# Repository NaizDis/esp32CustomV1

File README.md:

# esp32CustomV1
Custom esp32 model for personal Projects

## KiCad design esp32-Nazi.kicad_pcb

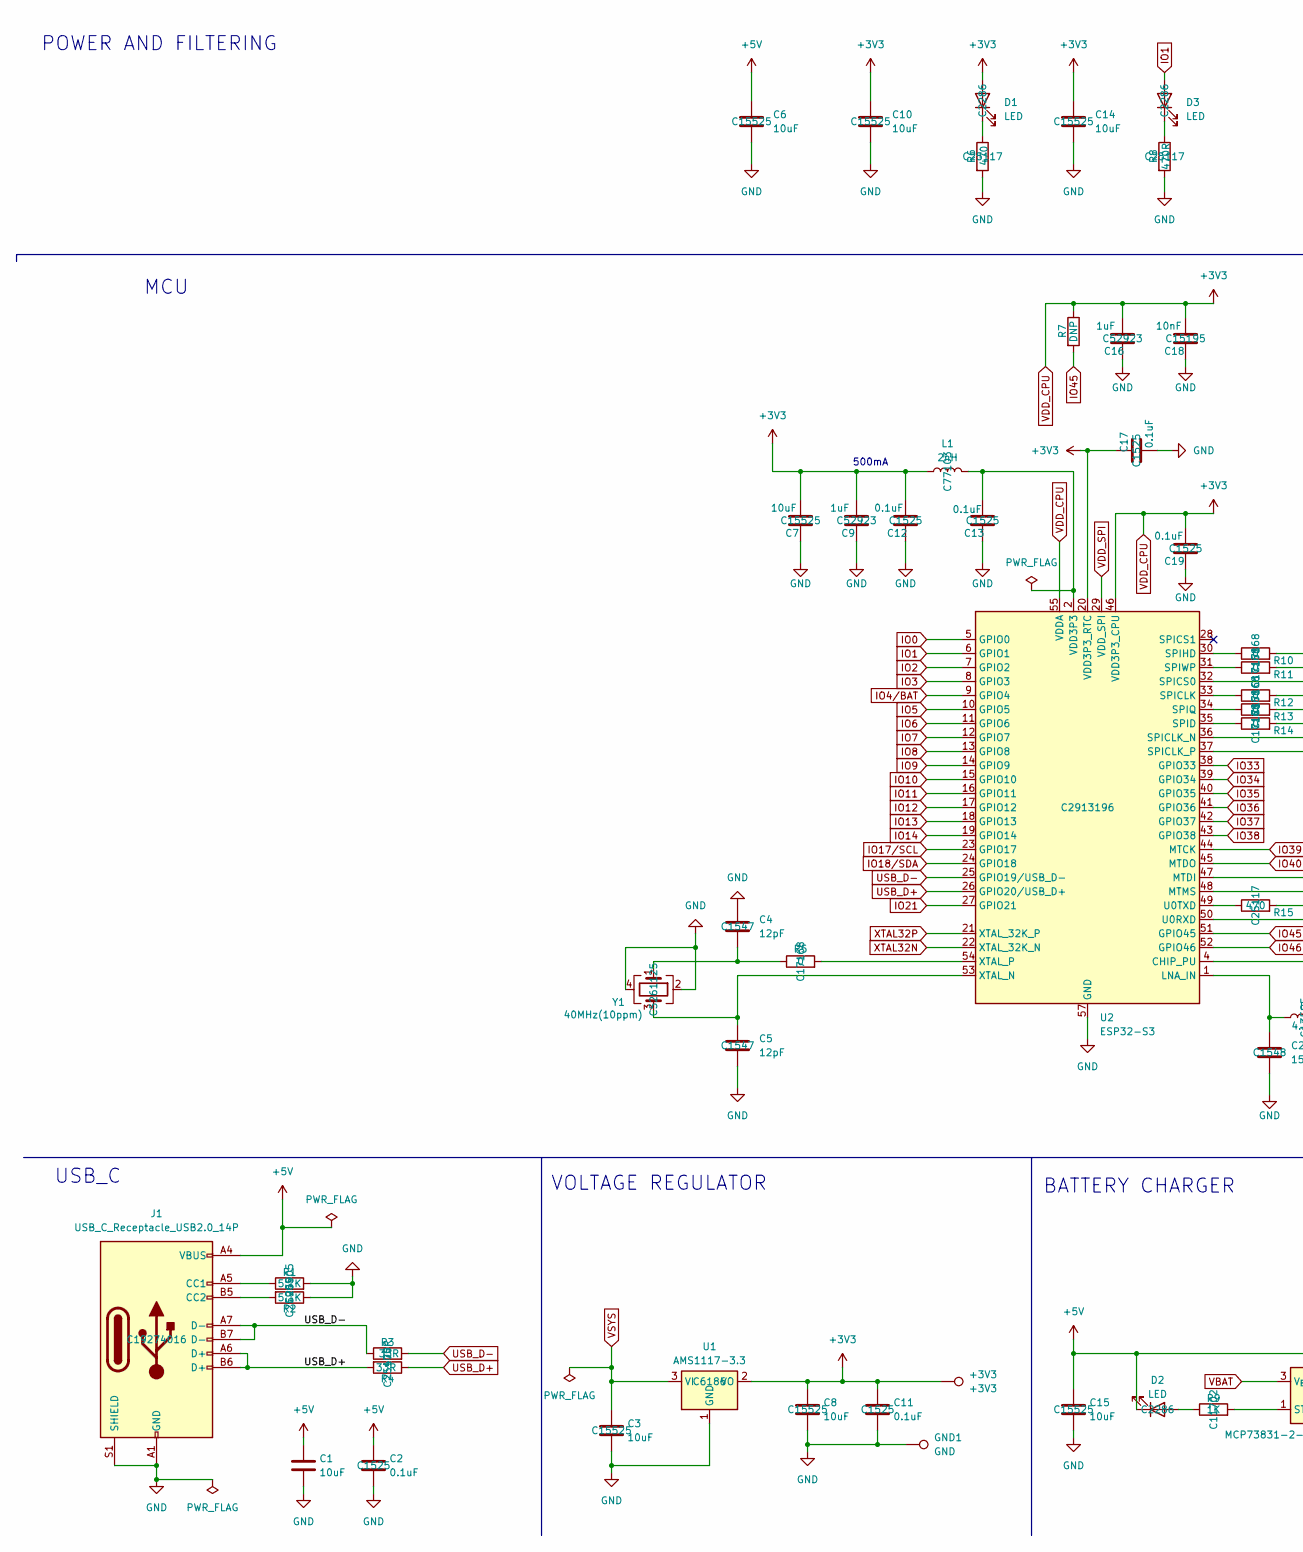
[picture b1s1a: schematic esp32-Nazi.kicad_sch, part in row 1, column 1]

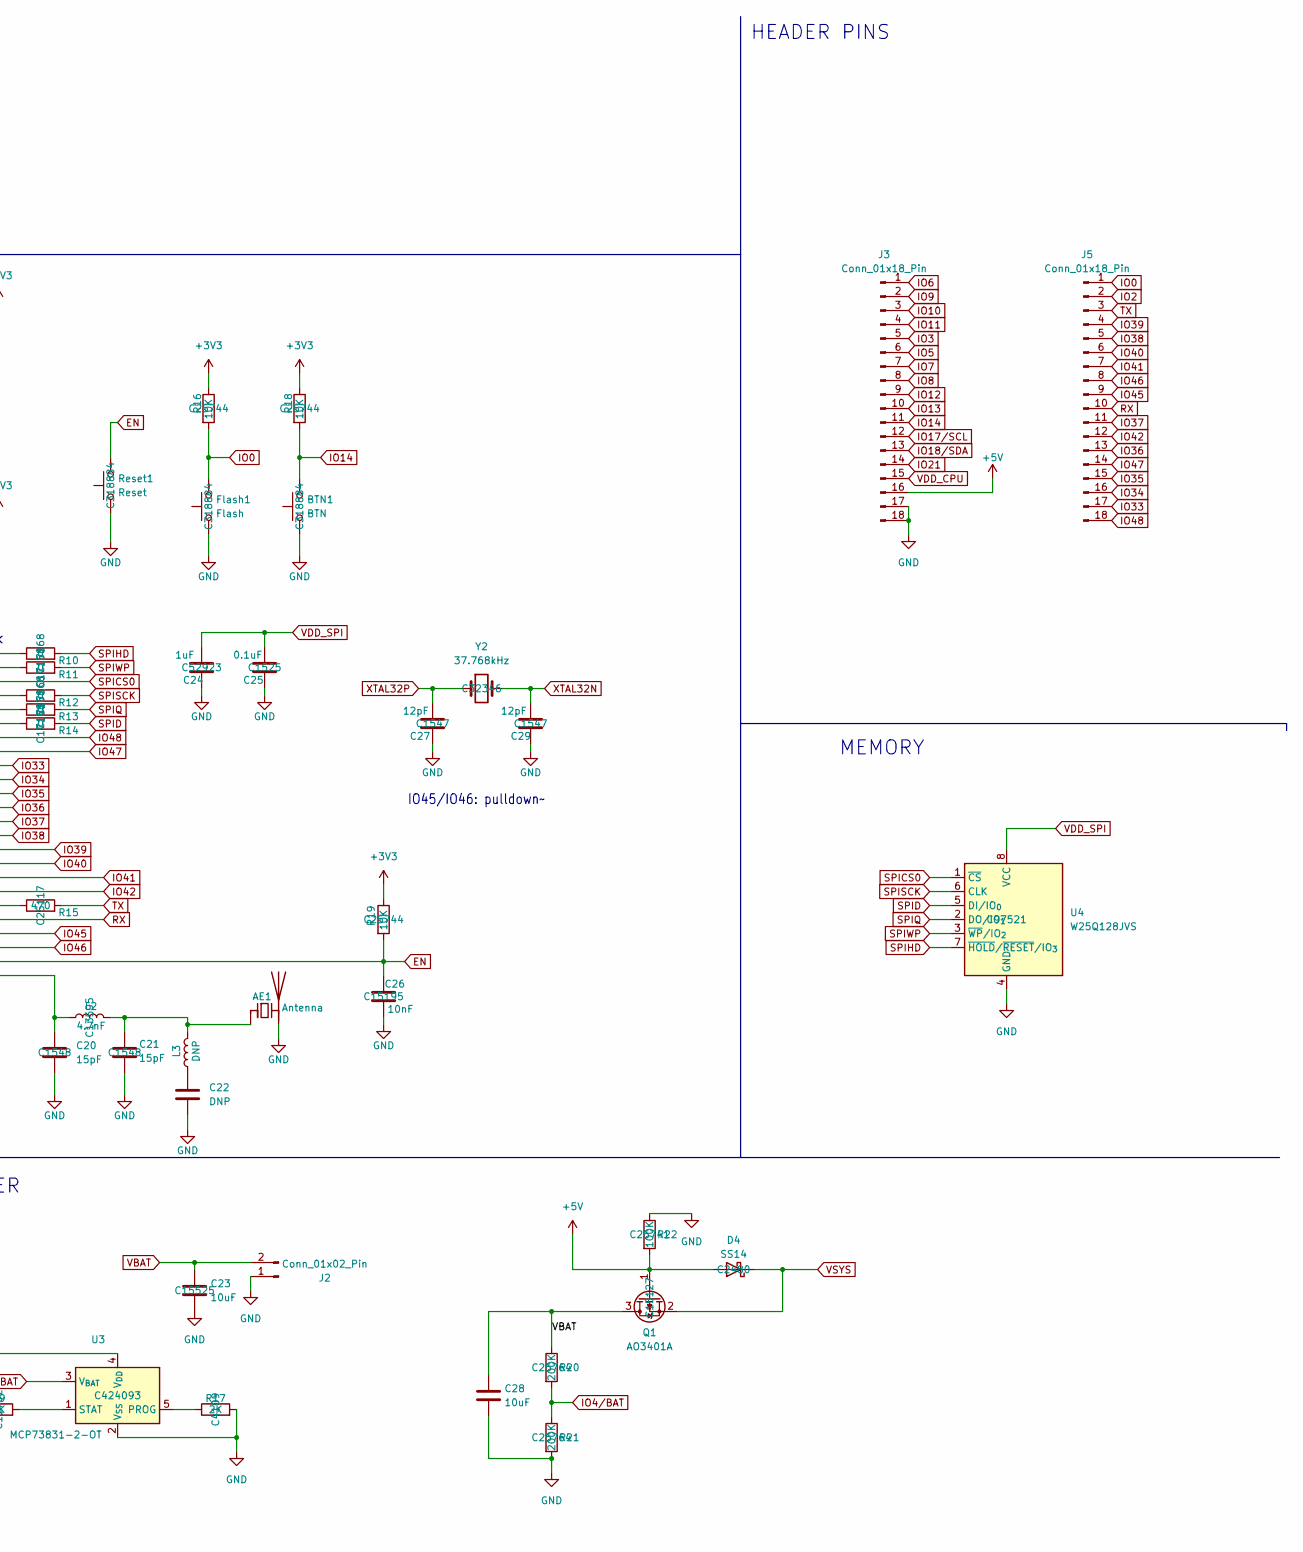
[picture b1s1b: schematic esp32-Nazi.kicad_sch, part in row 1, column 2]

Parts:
+3V3: +3V3; TestPoint_Pad_D1.0mm
AE1: Antenna; Texas_SWRA117D_2.4GHz_Left
BTN1: BTN; SW_Push_1P1T_XKB_TS-1187A; MNF PART NUMBER C318884
C1, C28: 10uF; C_0402_1005Metric
C2, C11, C12, C13, C17, C19, C25: 0.1uF; C_0402_1005Metric; MNF PART NUMBER C1525
C3, C6, C7, C8, C10, C14, C15, C23: 10uF; C_0402_1005Metric; MNF PART NUMBER C15525
C4, C5, C27, C29: 12pF; C_0402_1005Metric; MNF PART NUMBER C1547
C9, C16, C24: 1uF; C_0402_1005Metric; MNF PART NUMBER C52923
C18, C26: 10nF; C_0402_1005Metric; MNF PART NUMBER C15195
C20, C21: 15pF; C_0402_1005Metric; MNF PART NUMBER C1548
C22: DNP; C_0402_1005Metric
D1, D2, D3: LED; LED_0603_1608Metric; MNF PART NUMBER C2286
D4: SS14; D_SMA; MNF PART NUMBER C2480
Flash1: Flash; SW_Push_1P1T_XKB_TS-1187A; MNF PART NUMBER C318884
GND1: GND; TestPoint_Pad_D1.0mm
J1: USB_C_Receptacle_USB2.0_14P; USB_C_Receptacle_HCTL_HC-TYPE-C-16P-01A; MNF PART NUMBER C19274016
J2: Conn_01x02_Pin; PinSocket_1x02_P2.54mm_Vertical
J3, J5: Conn_01x18_Pin; PinHeader_1x18_P2.54mm_Vertical
L1: 2nH; L_0402_1005Metric; MNF PART NUMBER C77103
L2: 4.7nF; L_0402_1005Metric; MNF PART NUMBER C13595
L3: DNP; L_0402_1005Metric
Q1: AO3401A; SOT-23; MNF PART NUMBER C15127
R1, R2: 5.1K; R_0402_1005Metric; MNF PART NUMBER C25905
R3: 33R; R_0402_1005Metric; MNF PART NUMBER 470R
R4: 33R; R_0402_1005Metric; MNF PART NUMBER C25105
R5, R10, R11, R12, R13, R14: 0; R_0402_1005Metric; MNF PART NUMBER C17168
R6, R15: 470; R_0402_1005Metric; MNF PART NUMBER C25117
R7: DNP; R_0402_1005Metric
R8: 470R; R_0402_1005Metric; MNF PART NUMBER C25117
R9: 1K; R_0402_1005Metric; MNF PART NUMBER C11702
R16, R18, R19: 10K; R_0402_1005Metric; MNF PART NUMBER C25744
R17: 2K; R_0402_1005Metric; MNF PART NUMBER C4109
R20, R21: 200K; R_0402_1005Metric; MNF PART NUMBER C25764
R22: 100K; R_0402_1005Metric; MNF PART NUMBER C25741
Reset1: Reset; SW_Push_1P1T_XKB_TS-1187A; MNF PART NUMBER C318884
U1: AMS1117-3.3; SOT-223-3_TabPin2; MNF PART NUMBER C6186
U2: ESP32-S3; QFN-56-1EP_7x7mm_P0.4mm_EP4x4mm; MNF PART NUMBER C2913196
U3: MCP73831-2-OT; SOT-23-5; MNF PART NUMBER C424093
U4: W25Q128JVS; SOIC-8_5.3x5.3mm_P1.27mm; MNF PART NUMBER C97521
Y1: 40MHz(10ppm); Crystal_SMD_2520-4Pin_2.5x2.0mm; MNF PART NUMBER C5261125
Y2: 37.768kHz; Crystal_SMD_3215-2Pin_3.2x1.5mm; MNF PART NUMBER C32346

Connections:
+5V: C1.1, C2.1, C6.1, C15.1, D2.1 (K), D4.2 (A), J1.A4 (VBUS), J1.A9 (VBUS), J1.B4 (VBUS), J1.B9 (VBUS), J3.16, Q1.1 (G), R22.2, U3.4 (V_{DD})
EN: C26.1, R19.2, Reset1.2, U2.4 (CHIP_PU)
GND: AE1.2 (PCB_Trace), BTN1.1, C1.2, C2.2, C3.2, C4.1, C5.2, C6.2, C7.1, C8.2, C9.1, C10.2, C11.2, C12.1, C13.1, C14.2, C15.2, C16.1, C17.2, C18.1, C19.1, C20.2, C21.2, C22.2, C23.2, C24.1, C25.1, C26.2, C27.1, C28.2, C29.1, Flash1.1, GND1.1, J1.A1 (GND), J1.A12 (GND), J1.B1 (GND), J1.B12 (GND), J1.S1 (SHIELD), J2.1, J3.17, J3.18, R1.2, R2.1, R6.2, R8.2, R17.2, R21.2, R22.1, Reset1.1, U1.1 (GND), U2.57 (GND), U3.2 (V_{SS}), U4.4 (GND), Y1.2, Y1.4
IO0: Flash1.2, J5.1, R16.2, U2.5 (GPIO0)
IO1: D3.2 (A), U2.6 (GPIO1)
IO2: J5.2, U2.7 (GPIO2)
IO3: J3.5, U2.8 (GPIO3)
IO4/BAT: R20.2, R21.1, U2.9 (GPIO4)
IO5: J3.6, U2.10 (GPIO5)
IO6: J3.1, U2.11 (GPIO6)
IO7: J3.7, U2.12 (GPIO7)
IO8: J3.8, U2.13 (GPIO8)
IO9: J3.2, U2.14 (GPIO9)
IO10: J3.3, U2.15 (GPIO10)
IO11: J3.4, U2.16 (GPIO11)
IO12: J3.9, U2.17 (GPIO12)
IO13: J3.10, U2.18 (GPIO13)
IO14: BTN1.2, J3.11, R18.2, U2.19 (GPIO14)
IO17/SCL: J3.12, U2.23 (GPIO17)
IO18/SDA: J3.13, U2.24 (GPIO18)
IO21: J3.14, U2.27 (GPIO21)
IO33: J5.17, U2.38 (GPIO33)
IO34: J5.16, U2.39 (GPIO34)
IO35: J5.15, U2.40 (GPIO35)
IO36: J5.13, U2.41 (GPIO36)
IO37: J5.11, U2.42 (GPIO37)
IO38: J5.5, U2.43 (GPIO38)
IO39: J5.4, U2.44 (MTCK)
IO40: J5.6, U2.45 (MTDO)
IO41: J5.7, U2.47 (MTDI)
IO42: J5.12, U2.48 (MTMS)
IO45: J5.9, R7.2, U2.51 (GPIO45)
IO46: J5.8, U2.52 (GPIO46)
IO47: J5.14, U2.37 (SPICLK_P)
IO48: J5.18, U2.36 (SPICLK_N)
unnamed: AE1.1 (FEED), C21.1, L2.2, L3.2
unnamed: C4.2, R5.1, Y1.1
unnamed: C13.2, L1.2, U2.2 (VDD3P3), U2.3 (VDD3P3)
unnamed: C22.1, L3.1
unnamed: D1.1 (K), R6.1
unnamed: D2.2 (A), R9.1
unnamed: D3.1 (K), R8.1
unnamed: J1.A5 (CC1), R1.1
unnamed: J1.B5 (CC2), R2.2
unnamed: C20.1, L2.1, U2.1 (LNA_IN)
unnamed: R12.1, U2.33 (SPICLK)
unnamed: R14.1, U2.35 (SPID)
unnamed: R10.1, U2.30 (SPIHD)
unnamed: R13.1, U2.34 (SPIQ)
unnamed: R11.1, U2.31 (SPIWP)
unnamed: R15.1, U2.49 (U0TXD)
unnamed: C5.1, U2.53 (XTAL_N), Y1.3
unnamed: R5.2, U2.54 (XTAL_P)
unnamed: R17.1, U3.5 (PROG)
unnamed: R9.2, U3.1 (STAT)
RX: J5.10, U2.50 (U0RXD)
SPICS0: U2.32 (SPICS0), U4.1 (~CS)
SPID: R14.2, U4.5 (DI/IO_{0})
SPIHD: R10.2, U4.7 (~HOLD/~RESET/IO_{3})
SPIQ: R13.2, U4.2 (DO/IO_{1})
SPISCK: R12.2, U4.6 (CLK)
SPIWP: R11.2, U4.3 (~WP/IO_{2})
TX: J5.3, R15.2
USB_D+: J1.A6 (D+), J1.B6 (D+), R4.1, R4.2, U2.26 (GPIO20/USB_D+)
USB_D-: J1.A7 (D-), J1.B7 (D-), R3.1, R3.2, U2.25 (GPIO19/USB_D-)
VBAT: C23.1, C28.1, J2.2, Q1.3 (D), R20.1, U3.3 (V_{BAT})
VDD_CPU: +3V3.1, C7.2, C8.1, C9.2, C10.1, C11.1, C12.2, C14.1, C16.2, C17.1, C18.2, C19.2, D1.2 (A), J3.15, L1.1, R7.1, R16.1, R18.1, R19.1, U1.2 (VO), U2.20 (VDD3P3_RTC), U2.46 (VDD3P3_CPU), U2.55 (VDDA), U2.56 (VDDA)
VDD_SPI: C24.2, C25.2, U2.29 (VDD_SPI), U4.8 (VCC)
VSYS: C3.1, D4.1 (K), Q1.2 (S), U1.3 (VI)
XTAL32N: C29.2, U2.22 (XTAL_32K_N), Y2.2
XTAL32P: C27.2, U2.21 (XTAL_32K_P), Y2.1

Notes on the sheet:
USB_C
MEMORY
BATTERY CHARGER
MCU
HEADER PINS
IO45/IO46: pulldown~~{}
POWER AND FILTERING
500mA
VOLTAGE REGULATOR

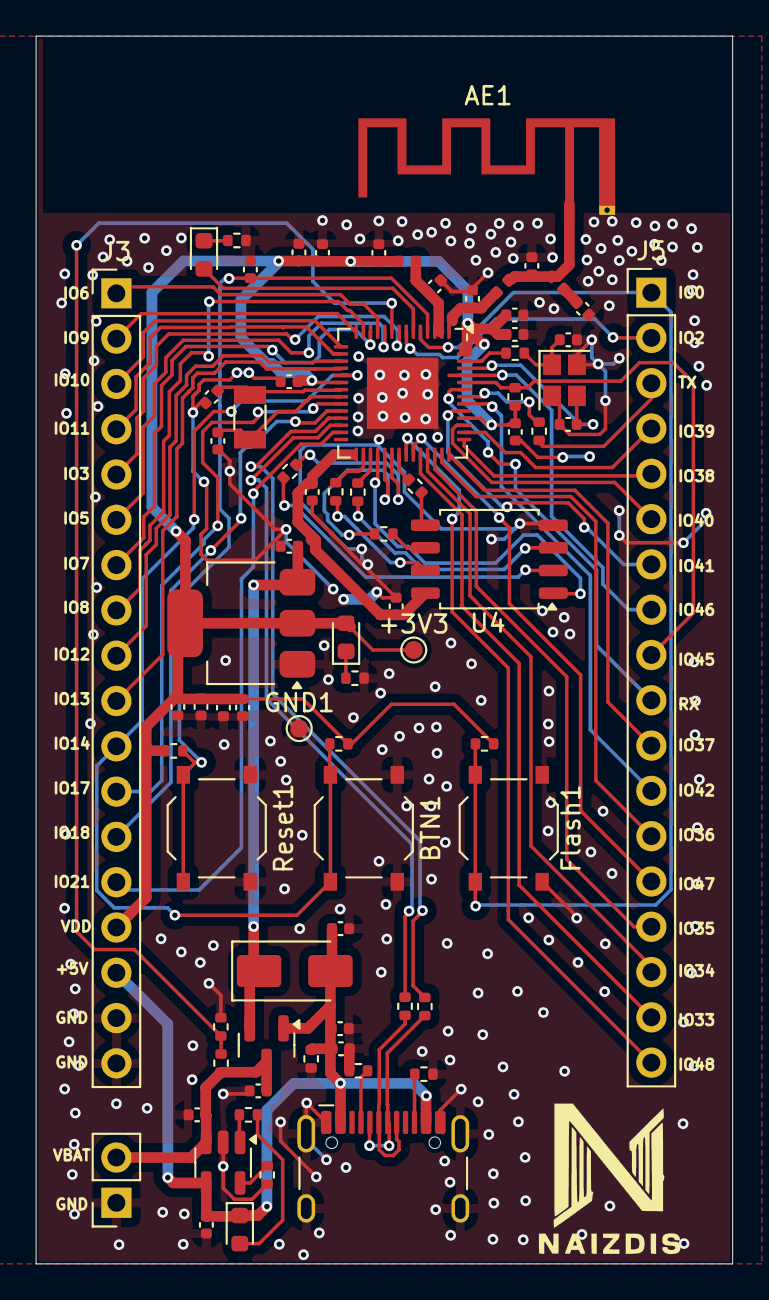
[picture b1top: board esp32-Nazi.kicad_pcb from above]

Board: 2 copper layers, 39.1 x 68.8 mm, 76 parts (0 on the bottom side), 71 nets.

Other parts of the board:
Gdfd: LOGO

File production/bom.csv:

Designator,Footprint,Quantity,Value,LCSC Part #
+3V3,TestPoint_Pad_D1.0mm,1,+3V3,
AE1,Texas_SWRA117D_2.4GHz_Left,1,Antenna,
BTN1,SW_Push_1P1T_XKB_TS-1187A,1,BTN,
"C1, C10, C14, C15, C23, C28, C3, C6, C7, C8",0402,10,10uF,
"C11, C12, C13, C17, C19, C2, C25",0402,7,0.1uF,
"C16, C24, C9",0402,3,1uF,
"C18, C26",0402,2,10nF,
"C20, C21",0402,2,15pF,
"C22, L3, R7",0402,3,DNP,
"C27, C29, C4, C5",0402,4,12pF,
"D1, D2, D3",0603,3,LED,
D4,D_SMA,1,SS14,
FLASH1,SW_Push_1P1T_XKB_TS-1187A,1,Flash,
GND1,TestPoint_Pad_D1.0mm,1,GND,
J1,USB_C_Receptacle_HCTL_HC-TYPE-C-16P-01A,1,USB_C_Receptacle_USB2.0_14P,
J2,PinSocket_1x02_P2.54mm_Vertical,1,Conn_01x02_Pin,
"J3, J5",PinHeader_1x18_P2.54mm_Vertical,2,Conn_01x18_Pin,
L1,0402,1,2nH,
L2,0402,1,4.7nF,
Q1,SOT-23,1,AO3401A,
"R1, R2",0402,2,5.1K,
"R10, R11, R12, R13, R14, R5",0402,6,0,
"R15, R6",0402,2,470,
"R16, R18, R19",0402,3,10K,
R17,0402,1,2K,
"R20, R21",0402,2,200K,
R22,0402,1,100K,
"R3, R4",0402,2,33R,
R8,0402,1,470R,
R9,0402,1,1K,
RESET1,SW_Push_1P1T_XKB_TS-1187A,1,Reset,
U1,SOT-223-3_TabPin2,1,AMS1117-3.3,
U2,QFN-56-1EP_7x7mm_P0.4mm_EP4x4mm,1,ESP32-S3,
U3,SOT-23-5,1,MCP73831-2-OT,
U4,SOIC-8_5.3x5.3mm_P1.27mm,1,W25Q128JVS,
Y1,Crystal_SMD_2520-4Pin_2.5x2.0mm,1,40MHz(10ppm),
Y2,Crystal_SMD_3215-2Pin_3.2x1.5mm,1,37.768kHz,

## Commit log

2025-11-03 schema-init
2025-11-04 pcb_init+gerbers
2025-11-04 production
2025-11-05 prductionJLPBC
